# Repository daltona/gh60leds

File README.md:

# gh60leds

This project is a LED backlight extension for the GH60 Rev C pcb\
It is a kicad project

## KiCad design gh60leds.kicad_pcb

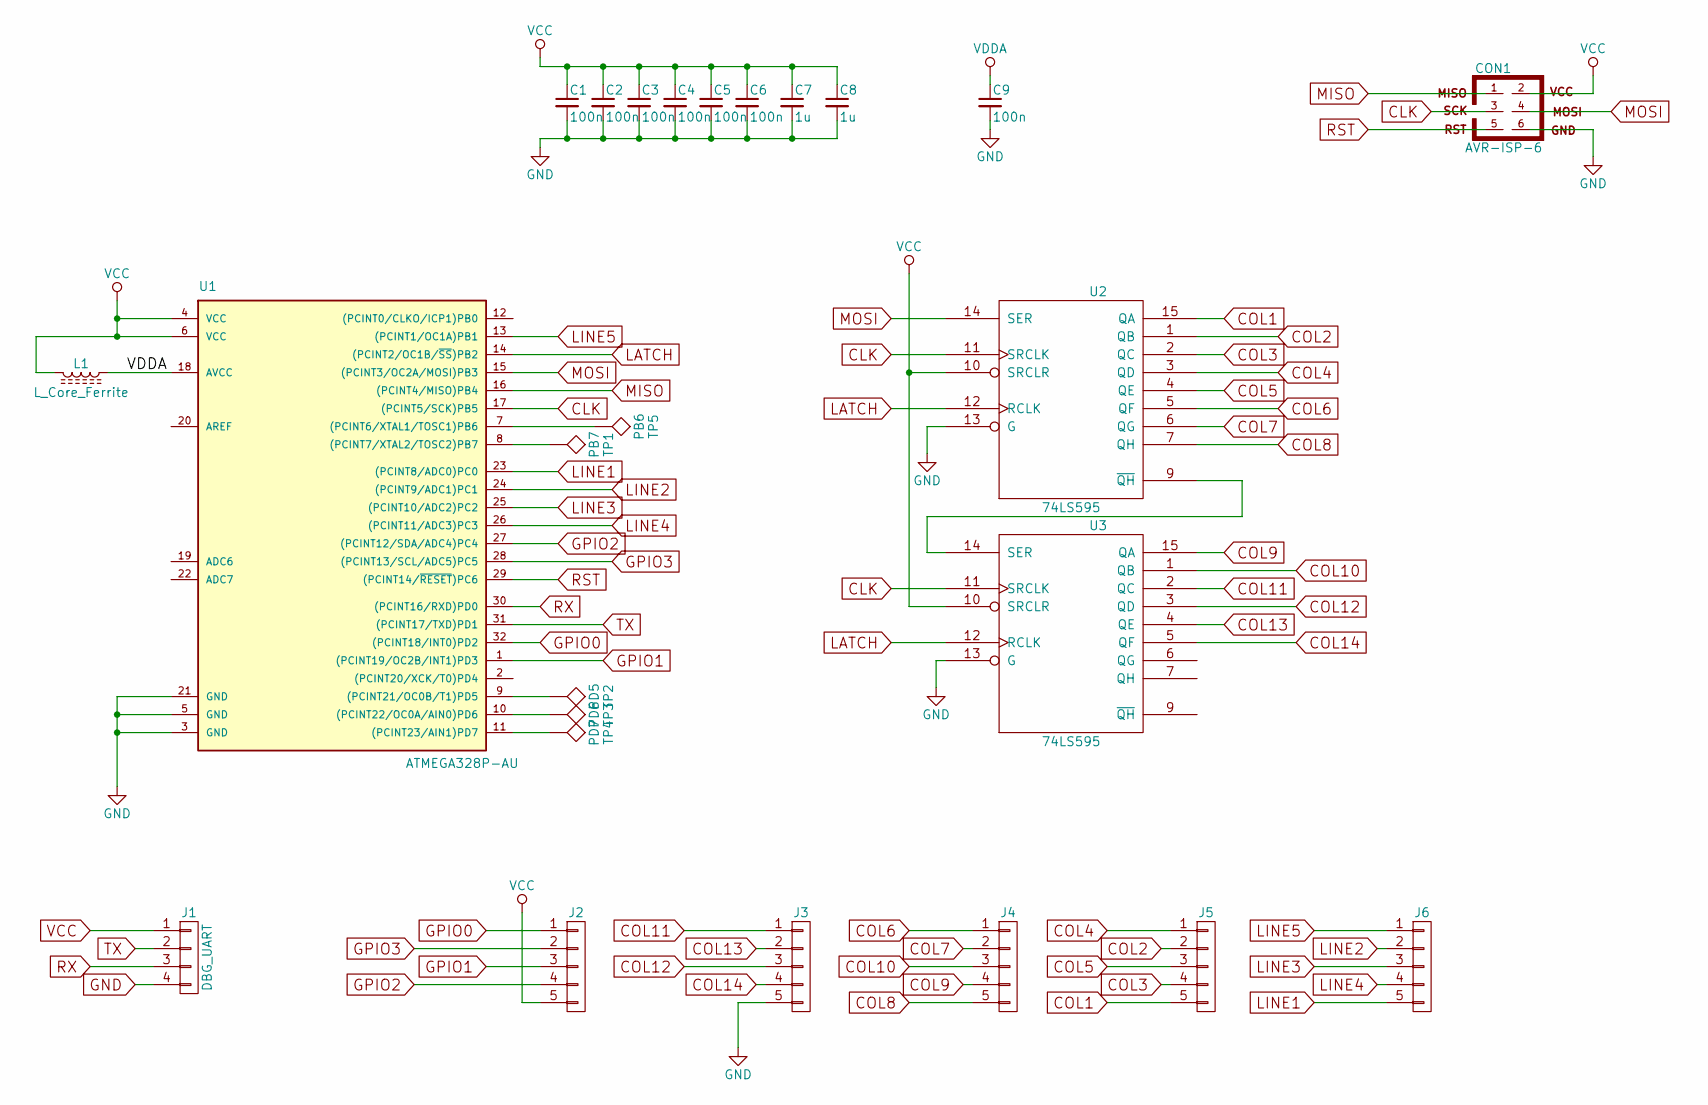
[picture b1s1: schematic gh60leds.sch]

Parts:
C1, C2, C3, C4, C5, C6, C9: 100n; C_0603
C7, C8: 1u; C_0603
CON1: AVR-ISP-6; Pin_Header_Straight_2x03_Pitch2.54mm
J1: DBG_UART; Pin_Header_Straight_1x04_Pitch2.54mm
J2, J3, J4, J5, J6: CONN_01X05; Pin_Header_Straight_1x05_Pitch2.54mm
L1: L_Core_Ferrite; L_0603
TP1: PB7; Measurement_Point_Square-SMD-Pad_Small
TP2: PD5; Measurement_Point_Square-SMD-Pad_Small
TP3: PD6; Measurement_Point_Square-SMD-Pad_Small
TP4: PD7; Measurement_Point_Square-SMD-Pad_Small
TP5: PB6; Measurement_Point_Square-SMD-Pad_Small
U1: ATMEGA328P-AU; TQFP-32_7x7mm_Pitch0.8mm
U2, U3: 74LS595; SOIC-16_3.9x9.9mm_Pitch1.27mm

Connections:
CLK: CON1.3, U1.17 ((PCINT5/SCK)PB5), U2.11 (SRCLK), U3.11 (SRCLK)
COL1: J5.5, U2.15 (QA)
COL2: J5.2, U2.1 (QB)
COL3: J5.4, U2.2 (QC)
COL4: J5.1, U2.3 (QD)
COL5: J5.3, U2.4 (QE)
COL6: J4.1, U2.5 (QF)
COL7: J4.2, U2.6 (QG)
COL8: J4.5, U2.7 (QH)
COL9: J4.4, U3.15 (QA)
COL10: J4.3, U3.1 (QB)
COL11: J3.1, U3.2 (QC)
COL12: J3.3, U3.3 (QD)
COL13: J3.2, U3.4 (QE)
COL14: J3.4, U3.5 (QF)
GND: C1.2, C2.2, C3.2, C4.2, C5.2, C6.2, C7.2, C8.2, C9.2, CON1.6, J1.4, J3.5, U1.3 (GND), U1.5 (GND), U1.21 (GND), U2.8 (GND), U2.13 (G), U3.8 (GND), U3.13 (G)
GPIO0: J2.1, U1.32 ((PCINT18/INT0)PD2)
GPIO1: J2.3, U1.1 ((PCINT19/OC2B/INT1)PD3)
GPIO2: J2.4, U1.27 ((PCINT12/SDA/ADC4)PC4)
GPIO3: J2.2, U1.28 ((PCINT13/SCL/ADC5)PC5)
LATCH: U1.14 ((PCINT2/OC1B/~SS~)PB2), U2.12 (RCLK), U3.12 (RCLK)
LINE1: J6.5, U1.23 ((PCINT8/ADC0)PC0)
LINE2: J6.2, U1.24 ((PCINT9/ADC1)PC1)
LINE3: J6.3, U1.25 ((PCINT10/ADC2)PC2)
LINE4: J6.4, U1.26 ((PCINT11/ADC3)PC3)
LINE5: J6.1, U1.13 ((PCINT1/OC1A)PB1)
MISO: CON1.1, U1.16 ((PCINT4/MISO)PB4)
MOSI: CON1.4, U1.15 ((PCINT3/OC2A/MOSI)PB3), U2.14 (SER)
unnamed: TP1.1, U1.8 ((PCINT7/XTAL2/TOSC2)PB7)
unnamed: TP2.1, U1.9 ((PCINT21/OC0B/T1)PD5)
unnamed: TP3.1, U1.10 ((PCINT22/OC0A/AIN0)PD6)
unnamed: TP4.1, U1.11 ((PCINT23/AIN1)PD7)
unnamed: TP5.1, U1.7 ((PCINT6/XTAL1/TOSC1)PB6)
unnamed: U2.9 (~QH), U3.14 (SER)
RST: CON1.5, U1.29 ((PCINT14/~RESET~)PC6)
RX: J1.3, U1.30 ((PCINT16/RXD)PD0)
TX: J1.2, U1.31 ((PCINT17/TXD)PD1)
VCC: C1.1, C2.1, C3.1, C4.1, C5.1, C6.1, C7.1, C8.1, CON1.2, J1.1, J2.5, L1.2, U1.4 (VCC), U1.6 (VCC), U2.10 (SRCLR), U2.16 (VCC), U3.10 (SRCLR), U3.16 (VCC)
VDDA: C9.1, L1.1, U1.18 (AVCC)

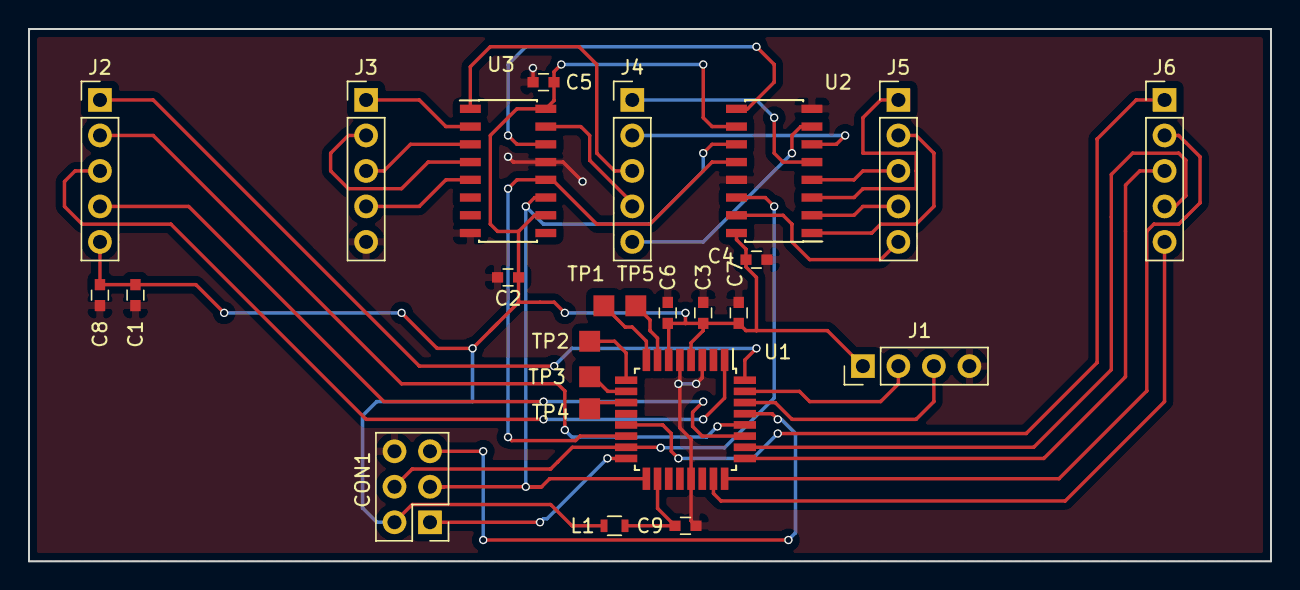
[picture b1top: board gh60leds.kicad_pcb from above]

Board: 2 copper layers, 88.9 x 38.1 mm, 25 parts (0 on the bottom side), 39 nets.
